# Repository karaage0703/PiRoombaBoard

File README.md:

# PiRoombaBoard
Raspberry Pi interface board with roomba

# Reference
- https://karaage.hatenadiary.jp/entry/2019/11/06/073000
- https://karaage.hatenadiary.jp/entry/2017/05/12/073000
- https://karaage.hatenadiary.jp/entry/2021/11/19/073000
- https://github.com/docofab/RoombaControlls

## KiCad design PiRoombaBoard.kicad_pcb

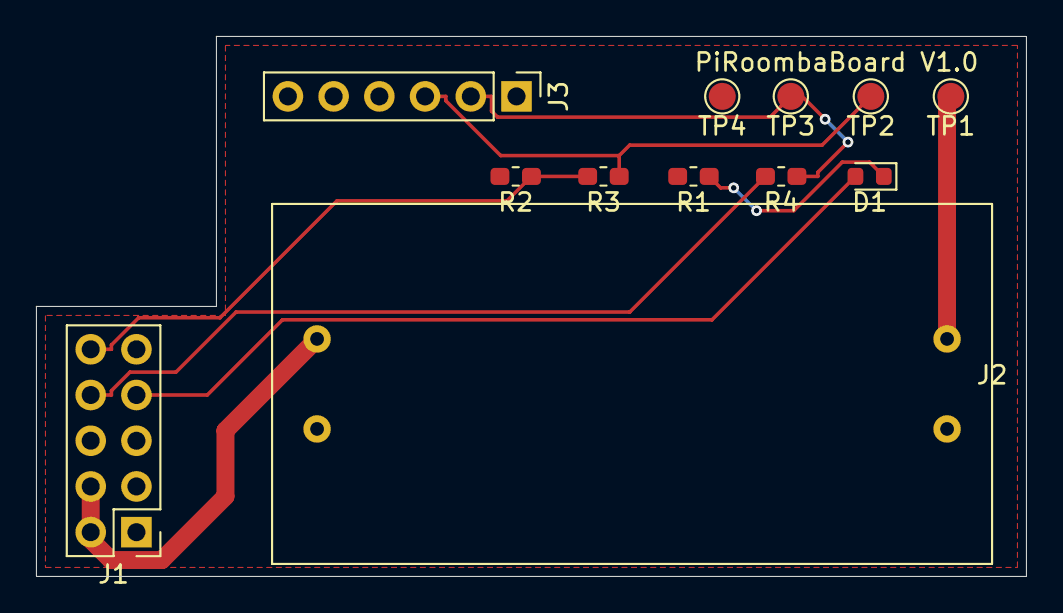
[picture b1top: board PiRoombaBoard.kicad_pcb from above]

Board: 2 copper layers, 55.0 x 30.0 mm, 12 parts (0 on the bottom side), 9 nets.

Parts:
D1: OSHR1608C1A; LED_0603_1608Metric
J1: Conn_02x05_Odd_Even; PinHeader_2x05_P2.54mm_Vertical
J2: Conn_01x04_Male; Pololu_D24V90F5
J3: Conn_01x06_Male; PinHeader_1x06_P2.54mm_Vertical
R1: 220; R_0603_1608Metric_Pad1.05x0.95mm_HandSolder
R2, R3, R4: 10k; R_0603_1608Metric_Pad1.05x0.95mm_HandSolder
TP1: PWR; TestPoint_Pad_D1.5mm
TP2: TX; TestPoint_Pad_D1.5mm
TP3: RX; TestPoint_Pad_D1.5mm
TP4: GND; TestPoint_Pad_D1.5mm

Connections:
+5V: J1.2, J1.4, J2.4
GND: J1.6, J1.9, J2.1, J2.3, J3.6, R1.2, R2.2, TP4.1
unnamed: D1.1, R1.1
unnamed: D1.2, J1.7
unnamed: J1.8, R4.2
unnamed: J1.10, R2.1, R3.2
unnamed: J2.2, TP1.1
unnamed: J3.2, R4.1, TP3.1
unnamed: J3.3, R3.1, TP2.1

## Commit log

2019-11-26 Add schematic
2021-11-13 Add script
2021-11-19 Refactoring
